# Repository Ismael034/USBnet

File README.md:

# USBnet

USBnet tunnels TCP connections between two computers over a single CH32V467WEU6 board. Plug the board into both computers with USB. The client exposes a local HTTP proxy and the server opens upstream TCP connections to the open internet.

## Why?

So... Did you notice that some computers have strict policies to avoid connecting USB devices except allowed ones such as keyboards and mice? What if we take advantage of the HID protocol inside these devices to send network packets? A translator would be required (the client and the server) but it is technically possible... Introducing... USBnet! Networking via USB (even if the USB device emulates a mouse) :D

## Host tool

```sh
uv sync --project usbnet
uv run --project usbnet usbnet --server   # on the server computer
uv run --project usbnet usbnet --client   # on the client computer
```

Point the client computer's proxy at `127.0.0.1:8080`.

## Modes

The client port can work in two ways. You pick one with `--config` (`--mode relay` or `--mode custom`), and `--client` figures out which one is active on its own.

- **Relay** (`relay`): the default. The board shows up as a USBnet device with a bulk endpoint. Fastest option.
- **Emulated** (`custom`): the board pretends to be another device, like a mouse or keyboard you cloned. The computer only sees that device, and the tunnel goes through a hidden HID feature report. Slower, but it blends in.

## Configuration

Hold the **USER** button while resetting to enter configuration mode. A USB interface should then appear as **USBnet Configuration** (`1a86:fe53`). Use `--config` to edit the profile stored in flash:

```sh
uv run --project usbnet usbnet --config list            # board and HID devices available to clone
uv run --project usbnet usbnet --config get             # print the stored profile
uv run --project usbnet usbnet --config clone 0 --preset mouse
uv run --project usbnet usbnet --config set --mode custom --preset keyboard
uv run --project usbnet usbnet --config set --defaults --yes
```

## Speed

Rough numbers from my tests. Yours may vary.

| Mode | Download | Upload | Ping (idle / loaded) |
| --- | --- | --- | --- |
| Relay | ~90 Mbps | ~88 Mbps | 3 / 4 ms |
| Emulated | ~25 Mbps | ~21 Mbps | 29 / 33 ms |

Relay is measured over a local link, so it's mostly the tunnel itself. Emulated is over the internet (speedtest.net), so it includes the line.

## Building

Download WCH's RISC-V toolchain from [MounRiver](https://www.mounriver.com/download) and put it under `toolchain/riscv32-wch-elf-gcc15`, or point `TOOLCHAIN_DIR` at another install.

```sh
make -C ch32v467
make -C ch32v467 test
```

## Tests

`make -C ch32v467 test` builds a hardware-test image. On reset it lights LED1–LED4 in order, then holds them on. Each LED maps to a function:

| Part | CH32V467 pin | Meaning |
| --- | --- | --- |
| LED1 | PA9 | Firmware heartbeat |
| LED2 | PA8 | USB1 enumerated |
| LED3 | PB10 | USB2 enumerated |
| LED4 | PB11 | USER pressed |

All four LEDs blinking together indicate firmware initialization failure.

## Flashing

Hold BOOT0 (PE12) while resetting, then flash with WCHISPTool_CMD v4.0:

```sh
WCHISPTool_CMD -p 0x00130000 -c ch32v467/CH32V467WEU6-isp.ini -o program -f ch32v467/build/ch32v467.bin
WCHISPTool_CMD -p 0x00130000 -c ch32v467/CH32V467WEU6-isp.ini -o verify -f ch32v467/build/ch32v467.bin
```

The board stays in the bootloader after flashing, so reset it (or replug) to start the new firmware.

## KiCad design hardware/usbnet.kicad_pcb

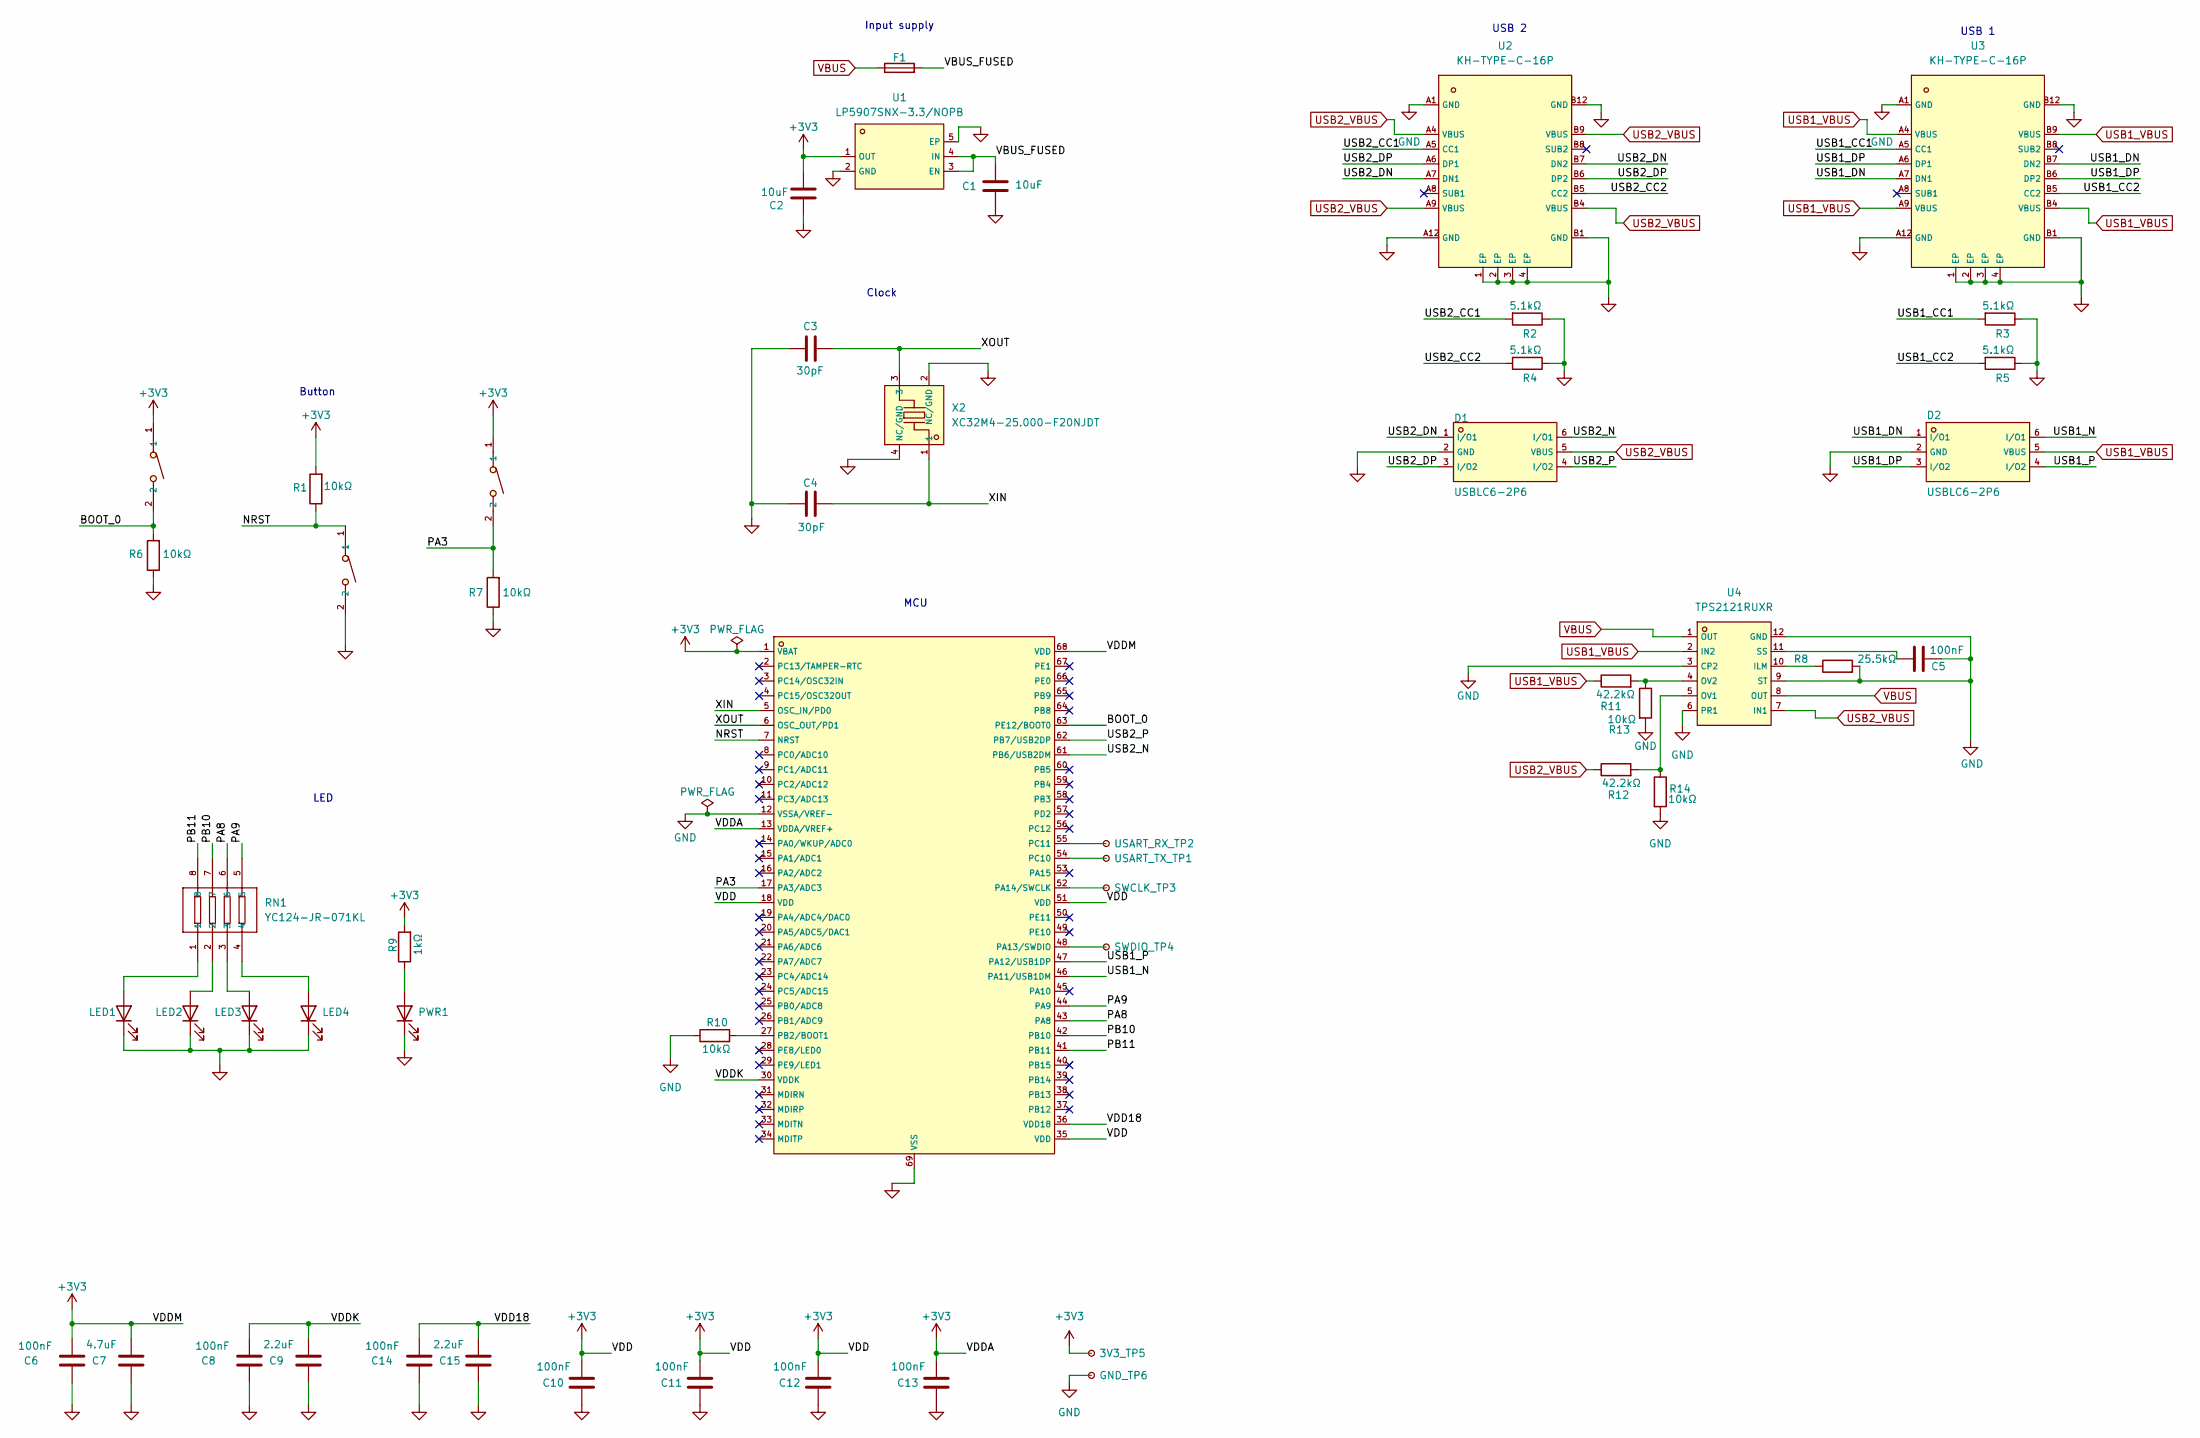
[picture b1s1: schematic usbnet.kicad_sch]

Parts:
3V3_TP5: TestPoint_Small; TestPoint_Pad_D1.0mm
BOOT0: TS-1088-AR02016; C720477_SW-SMD_L3_9-W3_0-P4_45; Manufacturer Part TS-1088-AR02016; LCSC Part Name 4*3*2mm 立贴 轻触开关
C1, C2: 10uF; C_0402_1005Metric; Voltage Rating 10V; Manufacturer Part CL05A106MP5NUNC; LCSC Part Name CAP CER 10uF 10V X5R 0402
C3, C4: 30pF; C_0402_1005Metric; Manufacturer Part CC0402JRNPO9BN300; LCSC Part Name 30pF ±5% 50V
C5: 100nF; C_0402_1005Metric; Manufacturer Part CL05B104KO5NNNC; LCSC Part Name 100nF ±10% 16V
C6, C8, C10, C11, C12, C13, C14: 100nF; C_0402_1005Metric; Manufacturer Part CC0402KRX7R7BB104; LCSC Part Name CAP CER 100nF 16V X7R 0402
C7: 4.7uF; C_0402_1005Metric; Manufacturer Part CL05A475KP5NRNC; LCSC Part Name CAP CER 4.7µF 10V X5R 0402
C9, C15: 2.2uF; C_0402_1005Metric; Manufacturer Part CL05A225MQ5NSNC; LCSC Part Name CAP CER 2.2µF 6.3V X5R 0402
D1, D2: USBLC6-2P6; C2827693_SOT-666-6_L1_6-W1_2-P0_50-LS1_6-BL; Manufacturer Part USBLC6-2P6; LCSC Part Name MSL=3
F1: JK-SMD0805-020-30V; Fuse_0805_2012Metric; Manufacturer Part JK-SMD0805-020-30V; LCSC Part Name 30V 200mA 0805自恢复
GND_TP6: TestPoint_Small; TestPoint_Pad_D1.0mm
LED1, LED2: XL-1608UYC-06; LED_0603_1608Metric; Manufacturer Part XL-1608UYC-06; LCSC Part Name XL-1608UYC-06
LED3: XL-1608UGC-04; LED_0603_1608Metric; Manufacturer Part XL-1608UGC-04; LCSC Part Name XL-1608UGC-04
LED4: NCD0603R1; LED_0603_1608Metric; Manufacturer Part NCD0603R1; LCSC Part Name NCD0603R1
PWR1: NCD0603R1; LED_0603_1608Metric; Manufacturer Part NCD0603R1; LCSC Part Name NCD0603R1
R1, R6, R7, R10, R13, R14: 10kΩ; R_0402_1005Metric; Manufacturer Part RC0402FR-0710KL; LCSC Part Name RES 10kΩ ±1% 62.5mW 0402
R2, R3, R4, R5: 5.1kΩ; R_0402_1005Metric; Manufacturer Part RC0402FR-075K1L; LCSC Part Name RES 5.1kΩ ±1% 62.5mW 0402
R8: 25.5kΩ; R_0402_1005Metric; Manufacturer Part RC0402FR-0725K5L; LCSC Part Name RES 25.5kΩ ±1% 62.5mW 0402
R9: 1kΩ; R_0402_1005Metric; Manufacturer Part 0402WGF1001TCE; LCSC Part Name 1kΩ ±1% 62.5mW 厚膜电阻
R11, R12: 42.2kΩ; R_0402_1005Metric; Manufacturer Part 0402WGF4222TCE; LCSC Part Name RES 42.2kΩ ±1% 62.5mW 0402
RESET1: TS-1088-AR02016; C720477_SW-SMD_L3_9-W3_0-P4_45; Manufacturer Part TS-1088-AR02016; LCSC Part Name 4*3*2mm 立贴 轻触开关
RN1: YC124-JR-071KL; C326869_RES-ARRAY-SMD_0804-8P-L2_0-W1_0-BL; LCSC C326869
SWCLK_TP3: TestPoint_Small; TestPoint_Pad_D1.0mm
SWDIO_TP4: TestPoint_Small; TestPoint_Pad_D1.0mm
U1: LP5907SNX-3.3/NOPB; C133572_ZQFN-4L_L1_0-W1_0-P0_63-BL-EP; LCSC C133572
U2, U3: KH-TYPE-C-16P; C709357_USB-C-SMD_KH-TYPE-C-16P; LCSC C709357
U4: TPS2121RUXR; C485916_VQFN-HR-12_L2_5-W2_0-P0_50-BL; LCSC C485916
U5: CH32V467WEU6; C55778389_QFN-68_L8_0-W8_0-P0_40-TL-EP5_5; LCSC C55778389
USART_RX_TP2: TestPoint_Small; TestPoint_Pad_D1.0mm
USART_TX_TP1: TestPoint_Small; TestPoint_Pad_D1.0mm
USER1: TS-1088-AR02016; C720477_SW-SMD_L3_9-W3_0-P4_45; Manufacturer Part TS-1088-AR02016; LCSC Part Name 4*3*2mm 立贴 轻触开关
X2: XC32M4-25.000-F20NJDT; C2842189_CRYSTAL-SMD_4P-L3_2-W2_5-BL; LCSC C2842189

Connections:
+3V3: 3V3_TP5.1, BOOT0.1, C2.2, C6.2, C7.2, C10.2, C11.2, C12.2, C13.2, R1.2, R9.2, U1.1 (OUT), U5.1 (VBAT), U5.13 (VDDA/VREF+), U5.18 (VDD), U5.35 (VDD), U5.51 (VDD), U5.68 (VDD), USER1.1; also elsewhere on the board
/BOOT_0: BOOT0.2, R6.2, U5.63 (PE12/BOOT0)
/NRST: R1.1, RESET1.1, U5.7 (NRST)
/PA3: R7.2, U5.17 (PA3/ADC3), USER1.2
/PA8: RN1.6, U5.43 (PA8)
/PA9: RN1.5, U5.44 (PA9)
/PB10: RN1.7, U5.42 (PB10)
/PB11: RN1.8, U5.41 (PB11)
/USB1_CC1: R3.2, U3.A5 (CC1)
/USB1_CC2: R5.2, U3.B5 (CC2)
/USB1_DN: D2.1 (I/O1), U3.A7 (DN1), U3.B7 (DN2)
/USB1_DP: D2.3 (I/O2), U3.A6 (DP1), U3.B6 (DP2)
/USB1_N: D2.6 (I/O1), U5.46 (PA11/USB1DM)
/USB1_P: D2.4 (I/O2), U5.47 (PA12/USB1DP)
/USB2_CC1: R2.2, U2.A5 (CC1)
/USB2_CC2: R4.2, U2.B5 (CC2)
/USB2_DN: D1.1 (I/O1), U2.A7 (DN1), U2.B7 (DN2)
/USB2_DP: D1.3 (I/O2), U2.A6 (DP1), U2.B6 (DP2)
/USB2_N: D1.6 (I/O1), U5.61 (PB6/USB2DM)
/USB2_P: D1.4 (I/O2), U5.62 (PB7/USB2DP)
/VBUS_FUSED: C1.2, F1.2, U1.3 (EN), U1.4 (IN)
/VDD18: C14.2, C15.2, U5.36 (VDD18)
/VDDK: C8.2, C9.2, U5.30 (VDDK)
/XIN: C4.2, U5.5 (OSC_IN/PD0), X2.1
/XOUT: C3.1, U5.6 (OSC_OUT/PD1), X2.3
GND: C1.1, C2.1, C3.2, C4.1, C5.2, C6.1, C7.1, C8.1, C9.1, C10.1, C11.1, C12.1, C13.1, C14.1, C15.1, D1.2 (GND), D2.2 (GND), GND_TP6.1, LED1.1 (K), LED2.1 (K), LED3.1 (K), LED4.1 (K), PWR1.1 (K), R2.1, R3.1, R4.1, R5.1, R6.1, R7.1, R8.2, R10.1, R13.2, R14.2, RESET1.2, U1.2 (GND), U1.5 (EP), U2.1 (EP), U2.2 (EP), U2.3 (EP), U2.4 (EP), U2.A1 (GND), U2.A12 (GND), U2.B1 (GND), U2.B12 (GND), U3.1 (EP), U3.2 (EP), U3.3 (EP), U3.4 (EP), U3.A1 (GND), U3.A12 (GND), U3.B1 (GND), U3.B12 (GND), U4.3 (CP2), U4.6 (PR1), U4.9 (ST), U4.12 (GND), U5.12 (VSSA/VREF-), U5.69 (VSS), X2.2 (NC/GND), X2.4 (NC/GND); also elsewhere on the board
unnamed: LED1.2 (A), RN1.1
unnamed: LED2.2 (A), RN1.2
unnamed: LED3.2 (A), RN1.3
unnamed: LED4.2 (A), RN1.4
unnamed: PWR1.2 (A), R9.1
unnamed: R8.1, U4.10 (ILM)
unnamed: R12.2, R14.1, U4.5 (OV1)
unnamed: R11.2, R13.1, U4.4 (OV2)
unnamed: C5.1, U4.11 (SS)
unnamed: SWDIO_TP4.1 (1_1), U5.48 (PA13/SWDIO)
unnamed: SWCLK_TP3.1 (1_1), U5.52 (PA14/SWCLK)
unnamed: R10.2, U5.27 (PB2/BOOT1)
unnamed: U5.54 (PC10), USART_TX_TP1.1 (1_1)
unnamed: U5.55 (PC11), USART_RX_TP2.1 (1_1)
USB1_VBUS: D2.5 (VBUS), R11.1, U3.A4 (VBUS), U3.A9 (VBUS), U3.B4 (VBUS), U3.B9 (VBUS), U4.2 (IN2)
USB2_VBUS: D1.5 (VBUS), R12.1, U2.A4 (VBUS), U2.A9 (VBUS), U2.B4 (VBUS), U2.B9 (VBUS), U4.7 (IN1)
VBUS: F1.1, U4.1 (OUT), U4.8 (OUT)

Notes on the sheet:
Clock
Button
Input supply
USB 2
USB 1
LED
MCU

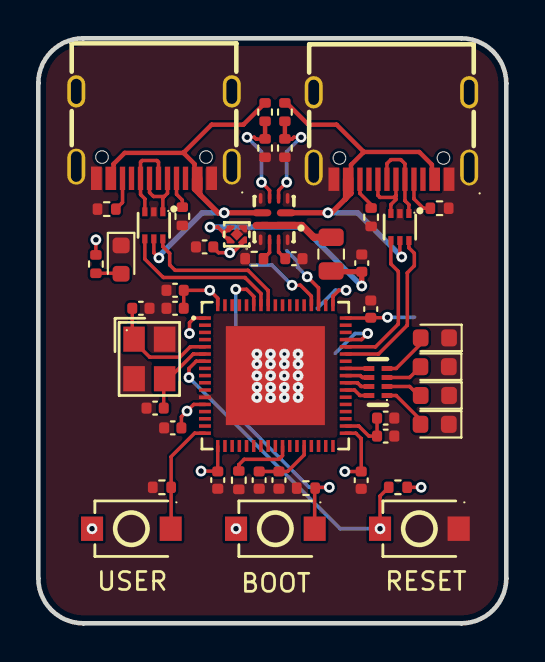
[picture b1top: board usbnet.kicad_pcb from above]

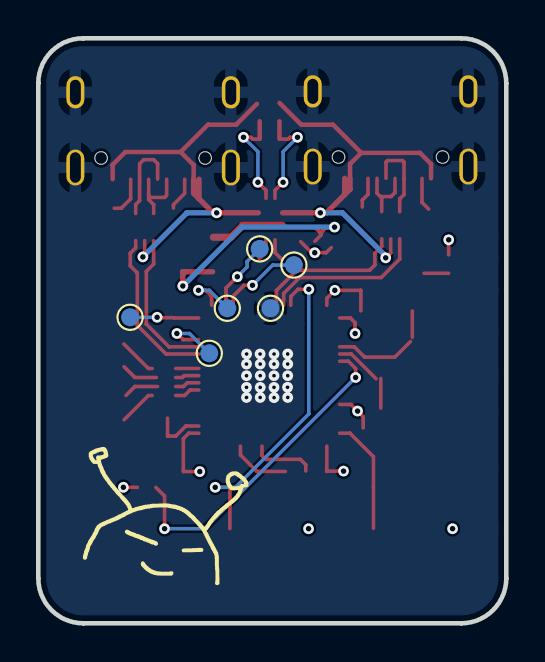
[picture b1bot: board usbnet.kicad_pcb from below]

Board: 4 copper layers, 26.0 x 32.5 mm, 53 parts (6 on the bottom side), 43 nets.

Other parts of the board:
SWDIO_TP5, SWDIO_TP6: TestPoint_Small; TestPoint_Pad_D1.0mm

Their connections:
+3V3: SWDIO_TP5.1 (1_1); also elsewhere on the board
GND: SWDIO_TP6.1 (1_1); also elsewhere on the board
